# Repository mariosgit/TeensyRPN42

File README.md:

# What ???

Trying to compile Free42 on a Teensy4.

It's a PlatformIO project, copied some code from free42 into lib and trying to compile it...

Allmost, just some link references to open/unlink/link file operations triggered from somethere ???

# Status

Ultraexperimental.

Works with double precision over terminal.

```
╒══════════════════════════════════════════════════════════════════════════════════════════════════════════════════╕
│                                                                                                                  │
│                                                                                                                  │
│             ▄▀▀▀▄       ▄▀▀▀▄ ▄▀▀▀▄ ▄▀▀▀▄ ▀▀▀▀█  ▄█   ▀▀▀▀█ ▄▀▀▀▄   ▄█  ▀▀▀▀█ ▄▀▀▀▄ ▄▀▀▀▄ ▄▄▄▄         ▄█        │
│ ▀▄ ▄▀ ▄       ▄▄▀       ▀▄▄▄█   ▄▄▀  ▄▄▄▀   ▄▀    █     ▄▀  █ ▄▀█ ▄▀ █    ▄▀    ▄▄▀  ▄▄▄▀ █▄▄   ▄▄▄▄    █        │
│   █   ▄     ▄▀     ▄▄      ▄▀ ▄▀    ▄   █  █      █    █    █▀  █ ▀▀▀█▀  █    ▄▀    ▄   █ █▄▄▄          █        │
│   ▀         ▀▀▀▀▀  ▀▀    ▀▀   ▀▀▀▀▀  ▀▀▀   ▀     ▀▀▀   ▀     ▀▀▀     ▀   ▀    ▀▀▀▀▀  ▀▀▀               ▀▀▀       │
│                    ▄█         ▀▀▀▀█ █▀▀▀▀  ▄▀▀  ▄▀▀▀▄ ▀▀▀▀█ ▄▀▀▀▄ █▀▀▀▀ █▀▀▀▀ ▄▀▀▀▄  ▄█   ▀▀▀▀█ ▄▄▄▄         ▄█  │
│ ▀▄ ▄▀ ▄     ▄▄▄▄    █           ▄▀  ▀▀▀▀▄ █▄▄▄   ▄▄▄▀   ▄▀   ▄▄▄▀ ▀▀▀▀▄ ▀▀▀▀▄ ▀▄▄▄▀   █     ▄▀  █▄▄   ▄▄▄▄    █  │
│  ▄▀▄  ▄             █    ▄▄    █    ▄   █ █   █ ▄   █  █    ▄   █ ▄   █ ▄   █ █   █   █    █    █▄▄▄          █  │
│ ▀   ▀              ▀▀▀   ▀▀    ▀     ▀▀▀   ▀▀▀   ▀▀▀   ▀     ▀▀▀   ▀▀▀   ▀▀▀   ▀▀▀   ▀▀▀   ▀                 ▀▀▀ │
╘══════════════════════════════════════════════════════════════════════════════════════════════════════════════════╛
T=0 
Z=0 
Y=2.92371704723␘-1 
X=-1.75637355817␘-1
```

# Software

* replaced scanf %e %g with own parser.

* quad precission ?
  * checking free42(swissmicro build process..)
    * gcc111libbid-arm64.a - lib src is packaged with it. And available on github
    * there is scanf stuff in ```common/core_phloat.cc``` only when not ARM build ?
    * cmd line:
    ```
    arm-none-eabi-g++ -Os -DDM42_OLDHW -I../common -DRELEASE -MMD -Wall -Wno-misleading-indentation -Wno-parentheses -Wno-write-strings -Wno-maybe-uninitialized -Wno-unknown-pragmas -Wno-class-memaccess -Wno-sign-compare -fno-exceptions -fno-rtti -DVERSION="\"3.3.8\"" -DDECIMAL_CALL_BY_REFERENCE=1 -DDECIMAL_GLOBAL_ROUNDING=1 -DDECIMAL_GLOBAL_ROUNDING_ACCESS_FUNCTIONS=1 -DDECIMAL_GLOBAL_EXCEPTION_FLAGS=1 -DDECIMAL_GLOBAL_EXCEPTION_FLAGS_ACCESS_FUNCTIONS=1 -D_WCHAR_T_DEFINED  -fdata-sections -ffunction-sections -Wl,--gc-sections -ggdb -mthumb -march=armv7e-m -mfloat-abi=hard -mfpu=fpv4-sp-d16 -DARM -DBCD_MATH -c -o core_phloat.o ../common/core_phloat.cc
    ```

  * It builds with the intel lib but it's a bit (way too) large
    ```
    ld: region `RAM' overflowed by 798408 bytes
    ld: region `FLASH' overflowed by 2006716 bytes
    ```

# Hardware

Ideas...

* STM32 ? F411RE - is dev board (Or F429? 82-168 IOs)
  ```
  RAM:   [=         ]   9.7% (used 12704 bytes from 131072 bytes)
  Flash: [======    ]  62.7% (used 328636 bytes from 524288 bytes)
  ```
  Connect to Nucleo STLink programmer part:
  * Remove SB13/SB14 for TX/RX connection to Nucleo MCU
  * Connect SWD (SWO not needed) (Open Jumpers to Nucleo MCU)
  * Connect TX->RX Rx->TX

* Display ???
  * OLED ? 256x64
  * VFD ?? cool but power usage ???
* Keys 
  * K.Choc low profile mechaniks
  * cheap 12mm clickers ?
  * RGB LEDs under keys ? SK6812-E | SK6805
* Power ?
  * Single Lipo ? Cheap Charger...

Start with a mini board ? Only the top three rows ? Uhm mhm might be tedious to map that, especially the func key top row ?

| | | | | | |
|----|---|---|---|---|---|
| +  | * | ^ | 7 | 8 | 9 |
| -  | / | . | 4 | 5 | 6 |
| ENTER || 0 | 1 | 2 | 3 |

# Refs

thomasokken's ingenious https://thomasokken.com/free42 https://github.com/aswild/free42

And code on github: https://github.com/swissmicros/free42

OpenRPNCalc ? on github, uses CubeIDE 🤯 and own code..

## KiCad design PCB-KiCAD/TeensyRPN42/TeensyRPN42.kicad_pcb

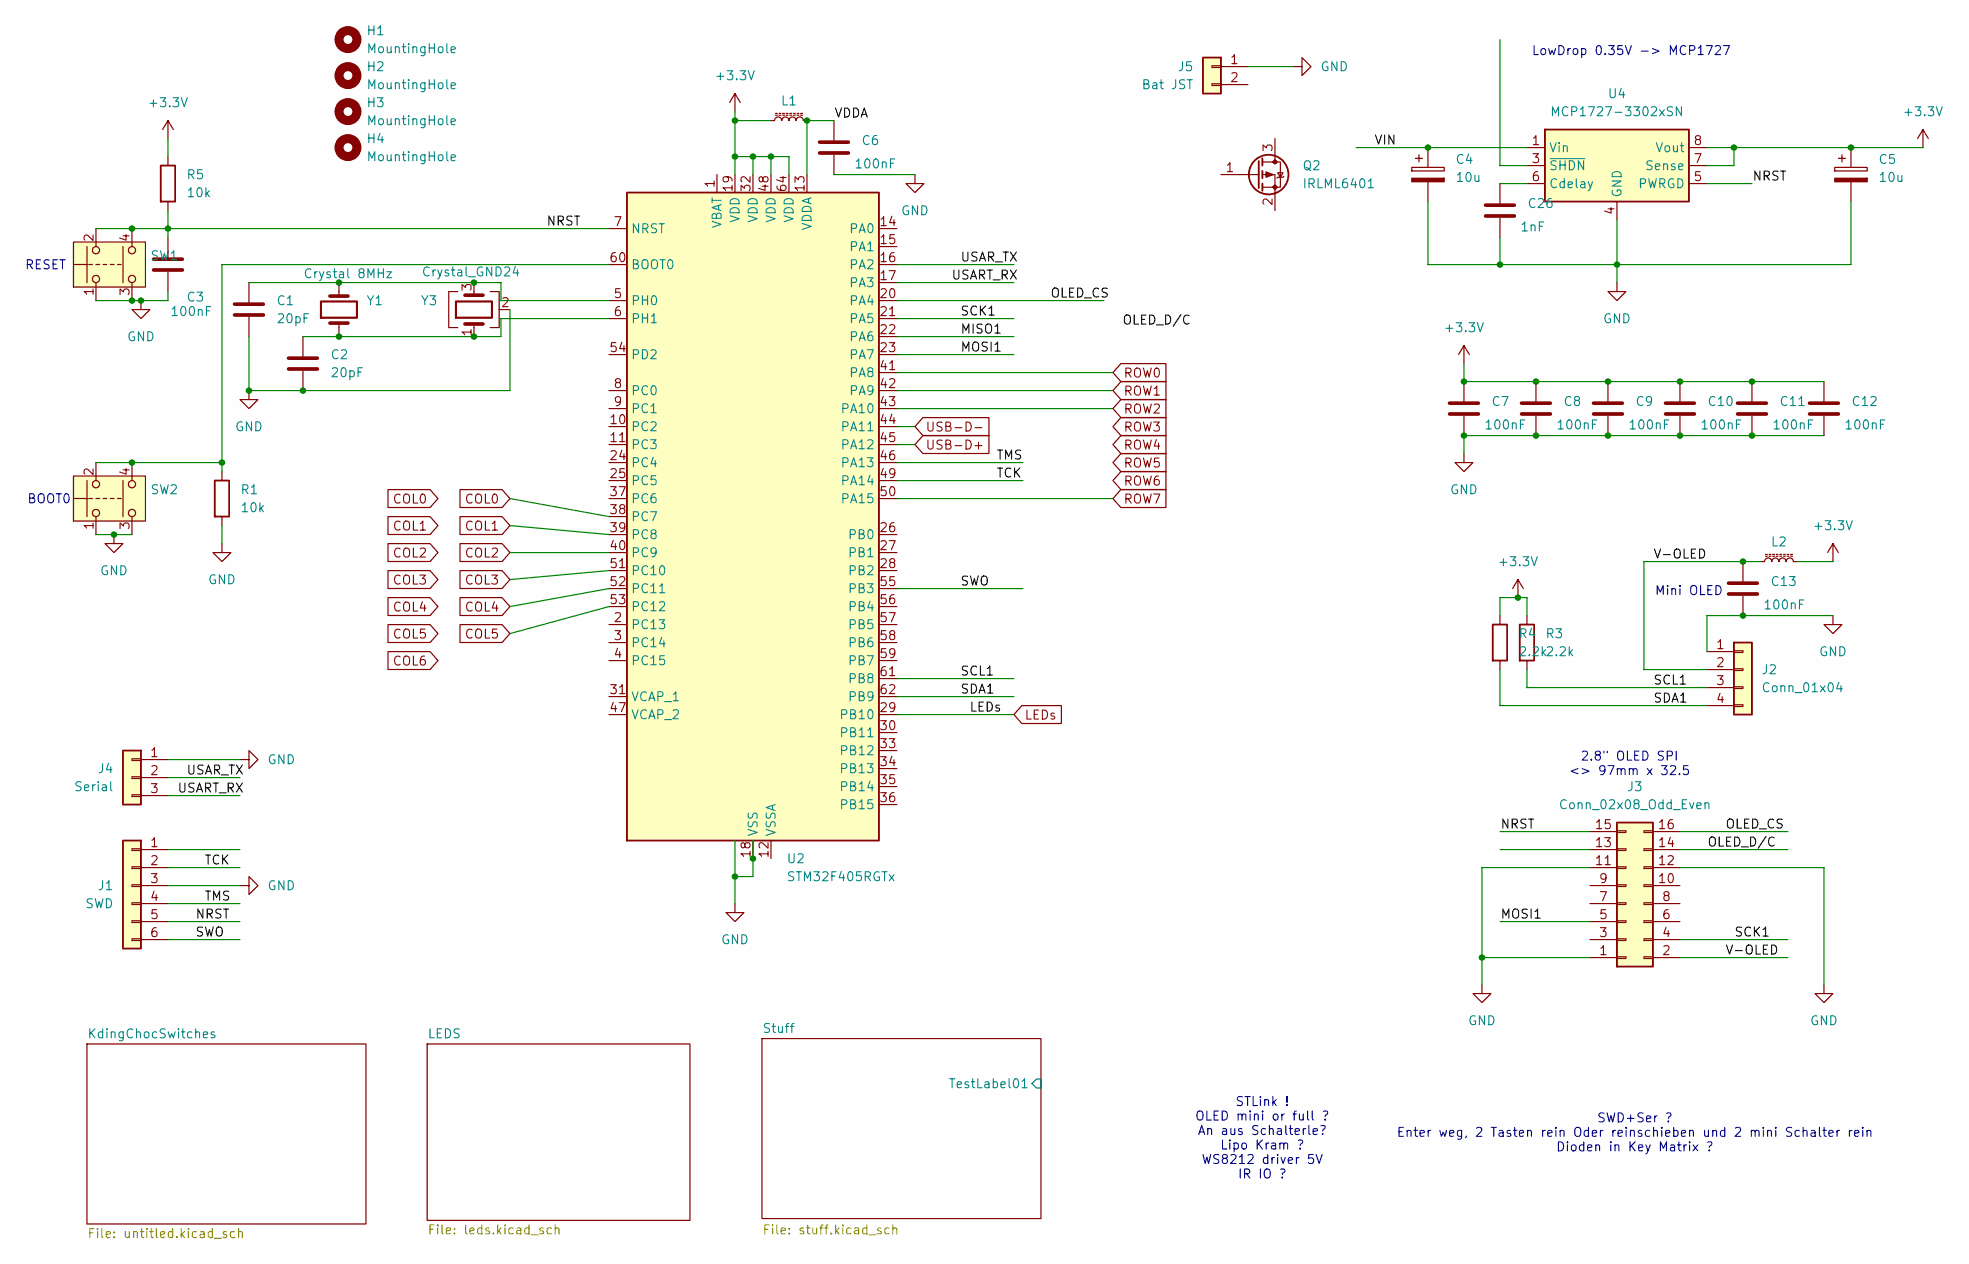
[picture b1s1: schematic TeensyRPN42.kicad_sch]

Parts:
C1, C2: 20pF; C_0603_1608Metric_Pad1.08x0.95mm_HandSolder
C3, C6, C7, C8, C9, C10, C11, C12, C13: 100nF; C_0603_1608Metric_Pad1.08x0.95mm_HandSolder
C4, C5: 10u; C_1206_3216Metric_Pad1.33x1.80mm_HandSolder
C26: 1nF; C_0603_1608Metric_Pad1.08x0.95mm_HandSolder
H1, H2, H3, H4: MountingHole; MountingHole_3.2mm_M3_ISO7380
J1: SWD; PinHeader_1x06_P2.54mm_Vertical
J2: Conn_01x04; PinSocket_1x04_P2.54mm_Vertical
J3: Conn_02x08_Odd_Even; OLED-2.8inch16pin
J4: Serial; PinHeader_1x03_P2.54mm_Vertical
J5: Bat JST; JST_EH_S2B-EH_1x02_P2.50mm_Horizontal
L1, L2: L_Ferrite_Small; L_0603_1608Metric_Pad1.05x0.95mm_HandSolder
Q2: IRLML6401; SOT-23
R1, R5: 10k; R_0603_1608Metric_Pad0.98x0.95mm_HandSolder
R3, R4: 2.2k; R_0603_1608Metric_Pad0.98x0.95mm_HandSolder
SW1, SW2: SW_Push_Dual; SW_SPST_EVQQ2
U2: STM32F405RGTx; LQFP-64_10x10mm_P0.5mm
U4: MCP1727-3302xSN; SOIC-8_3.9x4.9mm_P1.27mm
Y1: Crystal 8MHz; Crystal_SMD_HC49-SD_HandSoldering
Y3: Crystal_GND24; Crystal_SMD_0603-4Pin_6.0x3.5mm_HandSoldering

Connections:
+3.3V: C5.1, C7.1, C8.1, C9.1, C10.1, C11.1, C12.1, L1.1, L2.2, R3.1, R4.1, R5.1, U2.19 (VDD), U2.32 (VDD), U2.48 (VDD), U2.64 (VDD), U4.7 (Sense), U4.8 (Vout)
/MISO1: U2.22 (PA6)
/MOSI1: J3.5, U2.23 (PA7)
/NRST: C3.1, J1.5, J3.15, R5.2, SW1.2, SW1.4, U2.7 (NRST), U4.5 (PWRGD)
/OLED_CS: J3.16, U2.20 (PA4)
/OLED_D/C: J3.14
/SCK1: J3.4, U2.21 (PA5)
/SCL1: J2.3, R3.2, U2.61 (PB8)
/SDA1: J2.4, R4.2, U2.62 (PB9)
/SWO: J1.6, U2.55 (PB3)
/TCK: J1.2, U2.49 (PA14)
/TMS: J1.4, U2.46 (PA13)
/USART_RX: J4.3, U2.17 (PA3)
/USAR_TX: J4.2, U2.16 (PA2)
/V-OLED: C13.1, J2.2, J3.2, L2.1
/VDDA: C6.1, L1.2, U2.13 (VDDA)
/VIN: C4.1, U4.1 (Vin), U4.2 (Vin)
COL0: U2.38 (PC7); also elsewhere on the board
COL1: U2.39 (PC8); also elsewhere on the board
COL2: U2.40 (PC9); also elsewhere on the board
COL3: U2.51 (PC10); also elsewhere on the board
COL4: U2.52 (PC11); also elsewhere on the board
COL5: U2.53 (PC12); also elsewhere on the board
GND: C1.2, C2.2, C3.2, C4.2, C5.2, C6.2, C7.2, C8.2, C9.2, C10.2, C11.2, C12.2, C13.2, C26.2, J1.3, J2.1, J3.1, J3.11, J3.12, J4.1, J5.1, J5.2, R1.2, SW1.1, SW1.3, SW2.1, SW2.3, U2.18 (VSS), U2.63 (VSS), U4.4 (GND), Y3.2 (G), Y3.4 (G); also elsewhere on the board
LEDs: U2.29 (PB10); also elsewhere on the board
unnamed: R1.1, SW2.2, SW2.4, U2.60 (BOOT0)
unnamed: C1.1, U2.5 (PH0), Y1.2, Y3.3
unnamed: C2.1, U2.6 (PH1), Y1.1, Y3.1
unnamed: C26.1, U4.6 (Cdelay)
ROW0: U2.41 (PA8)
ROW1: U2.42 (PA9); also elsewhere on the board
ROW2: U2.43 (PA10); also elsewhere on the board
ROW7: U2.50 (PA15); also elsewhere on the board
USB-D+: U2.45 (PA12)
USB-D-: U2.44 (PA11)

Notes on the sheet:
SWD+Ser ? Enter weg, 2 Tasten rein Oder reinschieben und 2 mini Schalter rein Dioden in Key Matrix ?
BOOT0
RESET
2.8" OLED SPI <> 97mm x 32.5
Mini OLED
STLink ! OLED mini or full ? An aus Schalterle? Lipo Kram ? WS8212 driver 5V IR IO ?
LowDrop 0.35V -> MCP1727

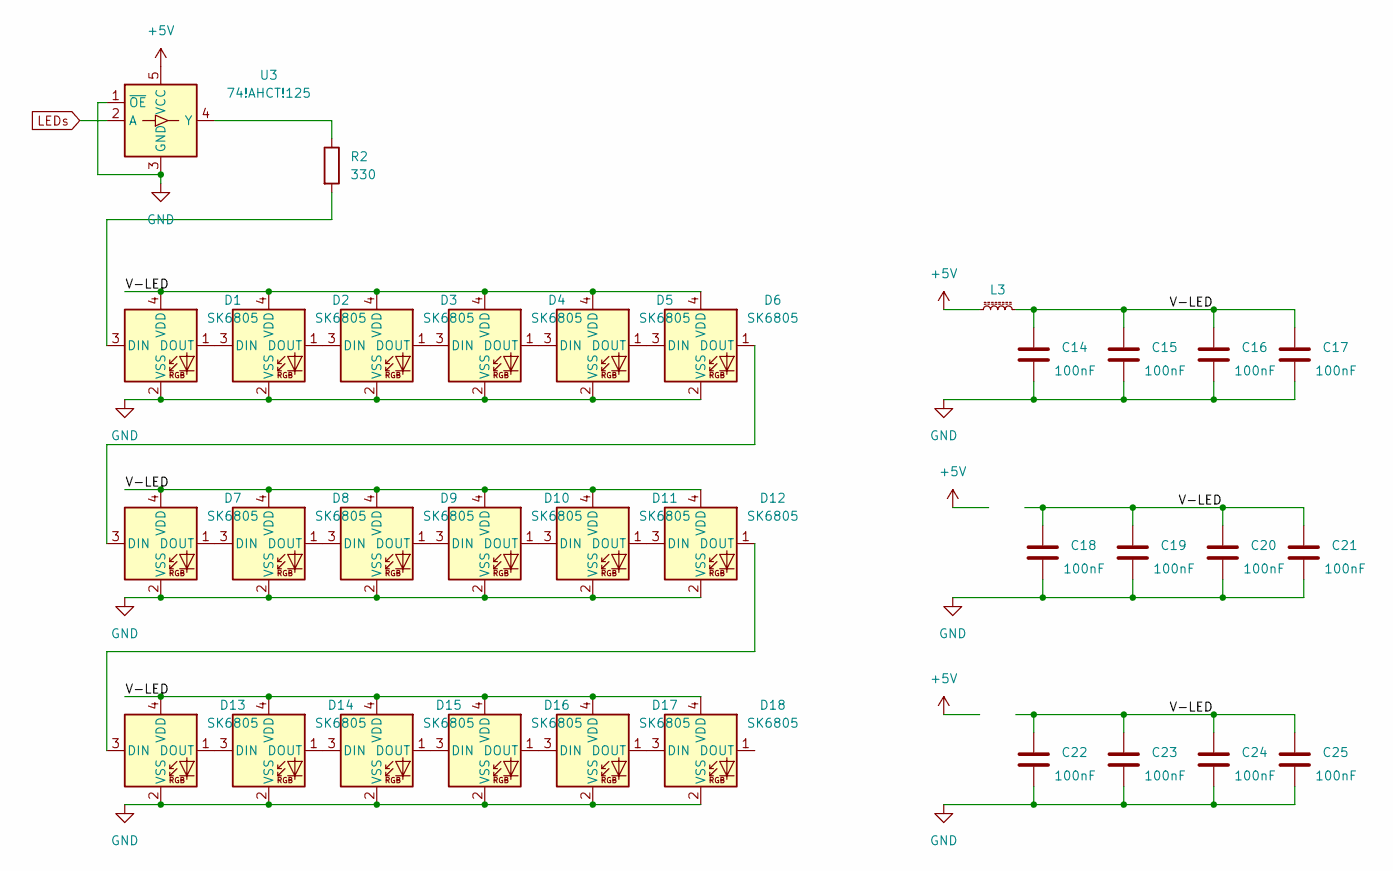
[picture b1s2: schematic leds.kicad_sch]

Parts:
C14, C15, C16, C17, C18, C19, C20, C21, C22, C23, C24, C25: 100nF; C_0603_1608Metric_Pad1.08x0.95mm_HandSolder
D1, D2, D3, D4, D5, D6, D7, D8, D9, D10, D11, D12, D13, D14, D15, D16, D17, D18: SK6805; LED_SK6805_PLCC4_2.4x2.7mm_P1.3mm
L3: L_Ferrite_Small; L_0603_1608Metric_Pad1.05x0.95mm_HandSolder
R2: 330; R_0603_1608Metric_Pad0.98x0.95mm_HandSolder
U3: 74!AHCT!125; SOT-353_SC-70-5

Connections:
+5V: L3.1, U3.5 (VCC)
/LEDS/V-LED: C14.1, C15.1, C16.1, C17.1, C18.1, C19.1, C20.1, C21.1, C22.1, C23.1, C24.1, C25.1, D1.4 (VDD), D2.4 (VDD), D3.4 (VDD), D4.4 (VDD), D5.4 (VDD), D6.4 (VDD), D7.4 (VDD), D8.4 (VDD), D9.4 (VDD), D10.4 (VDD), D11.4 (VDD), D12.4 (VDD), D13.4 (VDD), D14.4 (VDD), D15.4 (VDD), D16.4 (VDD), D17.4 (VDD), D18.4 (VDD), L3.2
GND: C14.2, C15.2, C16.2, C17.2, C18.2, C19.2, C20.2, C21.2, C22.2, C23.2, C24.2, C25.2, D1.2 (VSS), D2.2 (VSS), D3.2 (VSS), D4.2 (VSS), D5.2 (VSS), D6.2 (VSS), D7.2 (VSS), D8.2 (VSS), D9.2 (VSS), D10.2 (VSS), D11.2 (VSS), D12.2 (VSS), D13.2 (VSS), D14.2 (VSS), D15.2 (VSS), D16.2 (VSS), D17.2 (VSS), D18.2 (VSS), U3.1 (~OE), U3.3 (GND); also elsewhere on the board
LEDs: U3.2 (A); also elsewhere on the board
unnamed: D1.3 (DIN), R2.2
unnamed: D1.1 (DOUT), D2.3 (DIN)
unnamed: D2.1 (DOUT), D3.3 (DIN)
unnamed: D3.1 (DOUT), D4.3 (DIN)
unnamed: D4.1 (DOUT), D5.3 (DIN)
unnamed: D5.1 (DOUT), D6.3 (DIN)
unnamed: D6.1 (DOUT), D7.3 (DIN)
unnamed: D7.1 (DOUT), D8.3 (DIN)
unnamed: D8.1 (DOUT), D9.3 (DIN)
unnamed: D9.1 (DOUT), D10.3 (DIN)
unnamed: D10.1 (DOUT), D11.3 (DIN)
unnamed: D11.1 (DOUT), D12.3 (DIN)
unnamed: D12.1 (DOUT), D13.3 (DIN)
unnamed: D13.1 (DOUT), D14.3 (DIN)
unnamed: D14.1 (DOUT), D15.3 (DIN)
unnamed: D15.1 (DOUT), D16.3 (DIN)
unnamed: D16.1 (DOUT), D17.3 (DIN)
unnamed: D17.1 (DOUT), D18.3 (DIN)
unnamed: R2.1, U3.4 (Y)

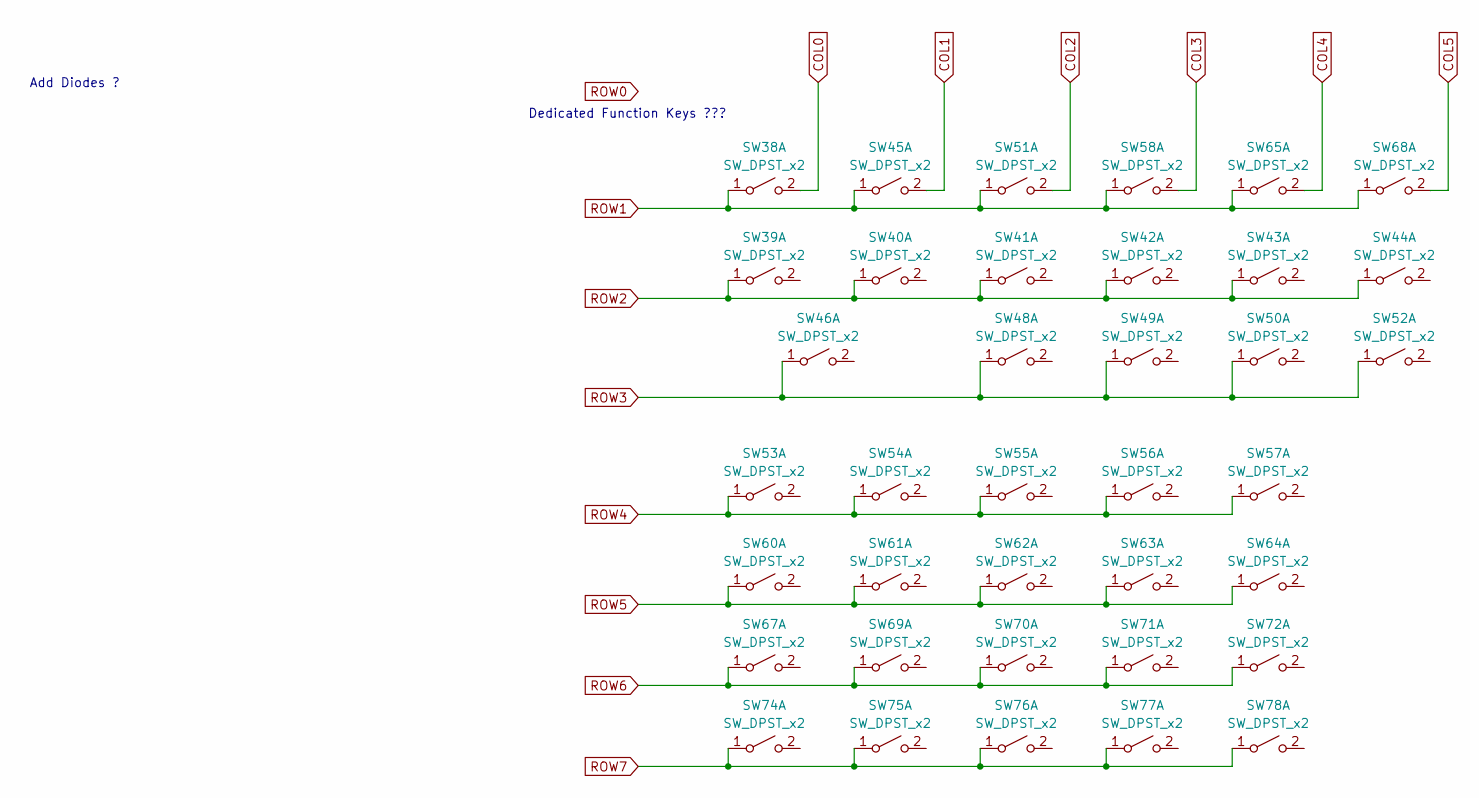
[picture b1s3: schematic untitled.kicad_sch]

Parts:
SW38, SW39, SW40, SW41, SW42, SW43, SW44, SW45, SW48, SW49, SW50, SW51, SW52, SW58, SW65, SW68: SW_DPST_x2; SW_Kailh_Choc_V1_1.00u
SW46: SW_DPST_x2; SW_Kailh_Choc_V1_2.00u
SW53, SW54, SW55, SW56, SW57, SW60, SW61, SW62, SW63, SW64, SW67, SW69, SW70, SW71, SW72, SW74, SW75, SW76, SW77, SW78: SW_DPST_x2; SW_Kailh_Choc_V1_1.25u

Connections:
COL0: SW38.2 (B); also elsewhere on the board
COL1: SW45.2 (B); also elsewhere on the board
COL2: SW51.2 (B); also elsewhere on the board
COL3: SW58.2 (B); also elsewhere on the board
COL4: SW65.2 (B); also elsewhere on the board
COL5: SW68.2 (B); also elsewhere on the board
ROW1: SW38.1 (A), SW45.1 (A), SW51.1 (A), SW58.1 (A), SW65.1 (A), SW68.1 (A); also elsewhere on the board
ROW2: SW39.1 (A), SW40.1 (A), SW41.1 (A), SW42.1 (A), SW43.1 (A), SW44.1 (A); also elsewhere on the board
ROW3: SW46.1 (A), SW48.1 (A), SW49.1 (A), SW50.1 (A), SW52.1 (A)
ROW4: SW53.1 (A), SW54.1 (A), SW55.1 (A), SW56.1 (A), SW57.1 (A)
ROW5: SW60.1 (A), SW61.1 (A), SW62.1 (A), SW63.1 (A), SW64.1 (A)
ROW6: SW67.1 (A), SW69.1 (A), SW70.1 (A), SW71.1 (A), SW72.1 (A)
ROW7: SW74.1 (A), SW75.1 (A), SW76.1 (A), SW77.1 (A), SW78.1 (A); also elsewhere on the board

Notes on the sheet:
Dedicated Function Keys ???
Add Diodes ?

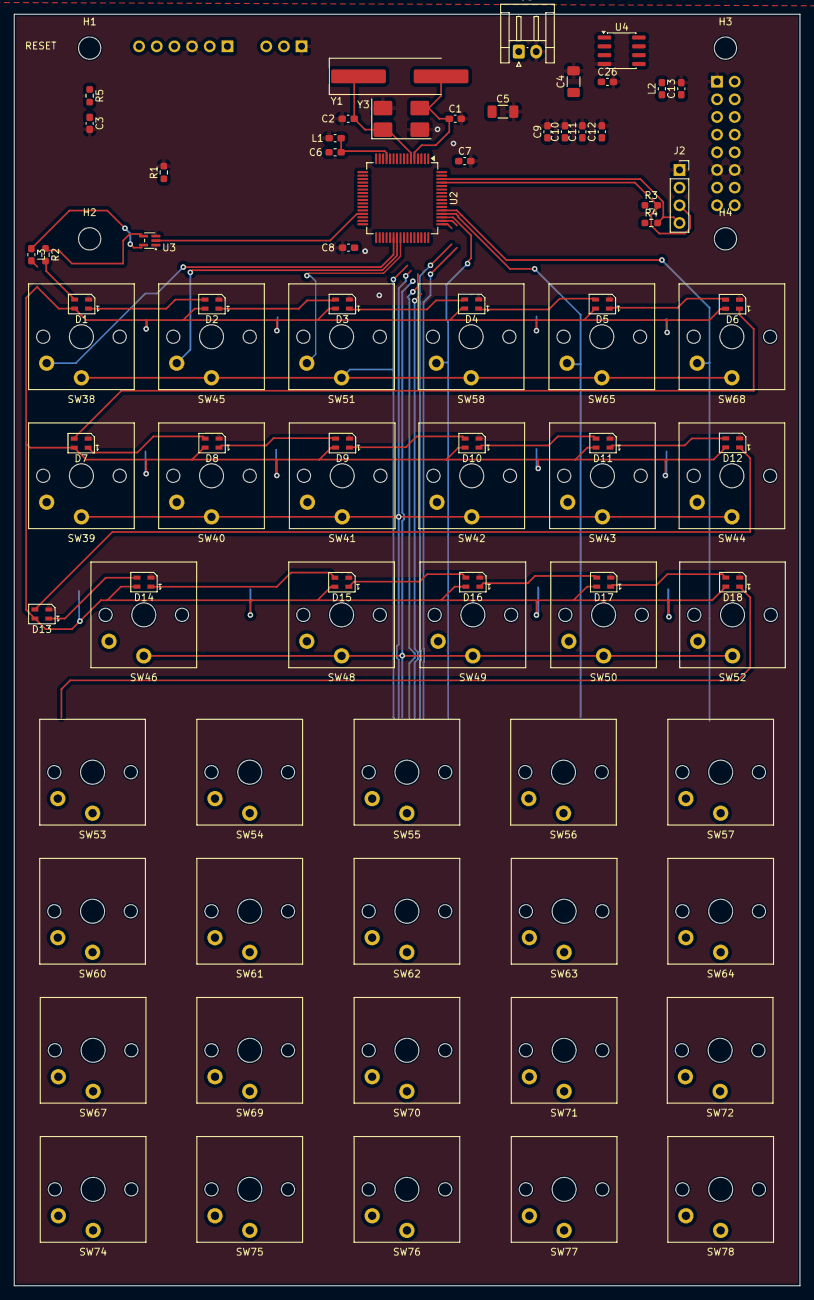
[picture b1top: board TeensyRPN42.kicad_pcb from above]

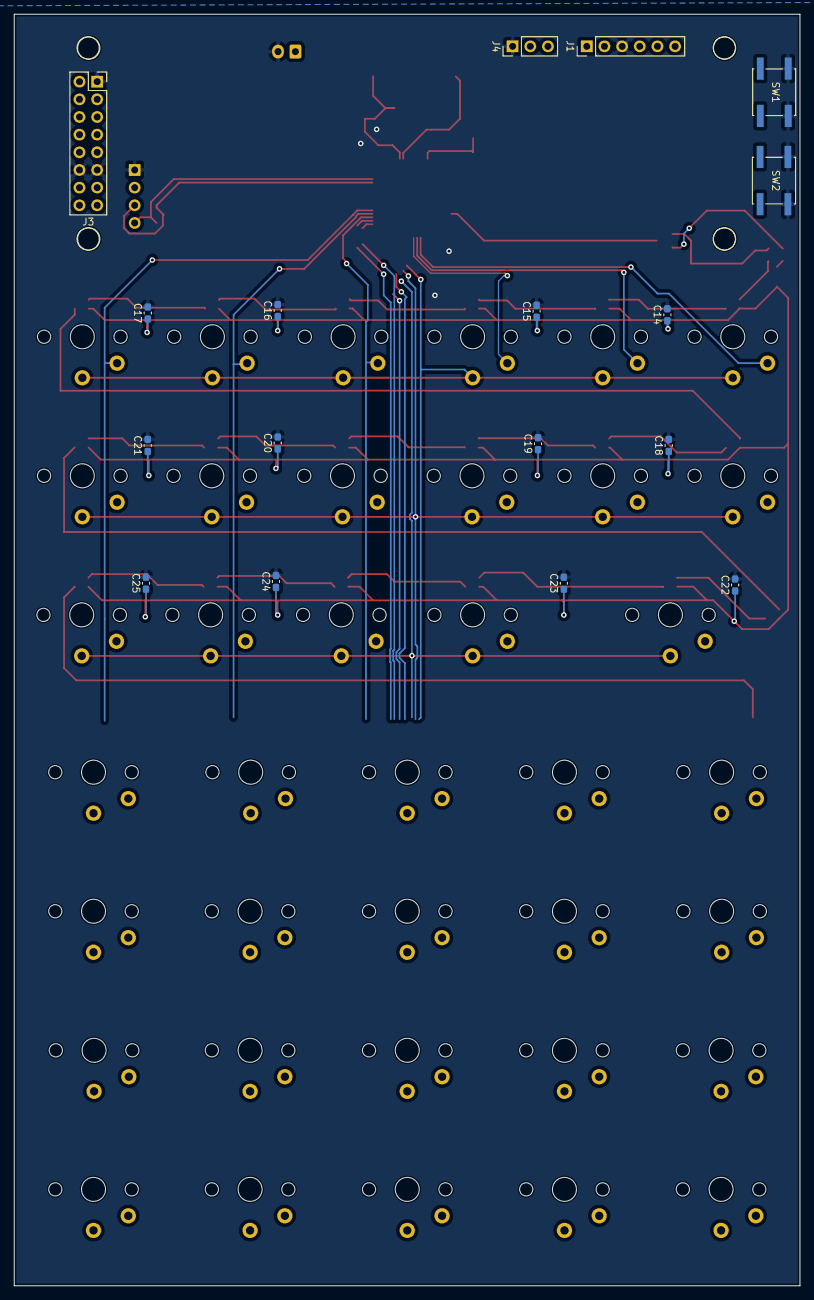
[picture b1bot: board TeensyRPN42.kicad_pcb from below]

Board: 2 copper layers, 113.0 x 182.9 mm, 105 parts (17 on the bottom side), 55 nets.

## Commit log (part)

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2024-03-08 Typo..
2024-03-12 Some optimizations..
2024-03-12 Trying console app..
2025-07-18 copied console app for reference.
2025-07-30 Added local
2025-07-31 stm32 test
2025-07-31 fix merge
2025-07-31 going native...
2025-11-09 Added KeyChoc stuff
2025-11-10 removed printfs
2025-11-10 Cleanup
2025-11-11 DebugStuff
2025-11-14 experiments with intel lib
2025-11-18 Oh signs of live with double preci
2025-11-18 A little PCBing
2025-11-22 more PCB
2026-02-06 more pcb ...
2026-02-12 kram
2026-02-12 More README...
2026-03-16 readme...
